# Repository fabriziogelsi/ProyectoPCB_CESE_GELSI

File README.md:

# ProyectoPCB_CESE_GELSI
Diseño de shield RF para portar a la EDU-CIAA

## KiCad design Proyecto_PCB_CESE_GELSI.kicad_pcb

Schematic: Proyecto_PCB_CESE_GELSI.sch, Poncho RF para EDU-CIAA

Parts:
ANT1: Antenna; antena
C1: 22uF; C_0805_HandSoldering; Digikey# 490-7611-1-ND
C2, C3, C4, C5, C6: 100nF; C_0805_HandSoldering; Digikey# 478-5266-1-ND
D2: LED_ALT; D_0805; Digikey# 475-1410-1-ND
F1, F2, F3: FIDUCIAL; Fiducial_1mm
IC1: SC2272L4; SSOP-20_5.3x7.2mm_Pitch0.65mm
IC2: ASM1117-33; SOT-223; Digikey# NCP1117ST50T3GOSCT-ND
IC3: SN74LVC1G125DCKR; SC-70-5; Digikey# 296-11604-1-ND
IC4: H5V3G
R2, R3: 1k; R_0805_HandSoldering; Digikey# 311-1.00KFRCT-ND
R4: 22; R_0805_HandSoldering; Digikey# 311-22ERCT-ND
R5: 620k; R_0805_HandSoldering; Digikey# 311-620KFRCT-ND
S1: SW SPDT; SW_SPDT; Digikey# 679-1847-6-ND
XA1: Conn_Poncho2P_2x_20x2; Conn_Poncho_Completo
Xbee1: XBee_Header; XBEE-HEADER; Digikey# 1528-1392-ND

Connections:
+3.3V: C3.1, C4.1, C5.1, IC2.2 (VO), IC3.5 (VCC), Xbee1.1 (VCC)
+5V: C1.1, C2.1, C6.1, IC1.20 (VCC), IC2.3 (VI), IC4.3 (VCC), XA1.2 (+5V), XA1.42 (+5V)
GND: C1.2, C2.2, C3.2, C4.2, C5.2, C6.2, D2.1 (K), IC1.9 (VSS), IC2.1 (GND/ADJ), IC3.1 (!OE!), IC3.3 (GND), IC4.2 (GND), IC4.6 (GND), XA1.43 (GND), XA1.79 (GND), Xbee1.10 (GND)
unnamed: ANT1.1, IC4.1 (ANT)
unnamed: D2.2 (A), R2.2
unnamed: IC1.1 (A0), XA1.66 (lcd3)
unnamed: IC1.2 (A1), XA1.68 (lcd2)
unnamed: IC1.3 (A2), XA1.70 (lcd1)
unnamed: IC1.4 (A3), XA1.72 (GPIO1)
unnamed: IC1.5 (A4), XA1.74 (GPIO3)
unnamed: IC1.6 (A5), XA1.76 (GPIO5)
unnamed: IC1.7 (A6), XA1.78 (GPIO7)
unnamed: IC1.8 (A7), XA1.80 (GPIO8)
unnamed: IC1.12 (A8), XA1.75 (GPIO6)
unnamed: IC1.13 (A9), XA1.73 (GPIO4)
unnamed: IC1.14 (A10), XA1.71 (GPIO2)
unnamed: IC1.15 (A11), XA1.69 (GPIO0)
unnamed: IC1.16 (DIN), IC4.4 (DAT), IC4.5 (DAT)
unnamed: IC1.17 (OSCO), R5.1
unnamed: IC1.18 (OSCI), R5.2
unnamed: IC1.19 (VT), XA1.63 (lcdEN)
unnamed: IC3.2 (A), R3.1
unnamed: IC3.4 (Y), Xbee1.3 (DIN/~CONFIG)
unnamed: R2.1, Xbee1.15 (Assoc./AD5/DIO5)
unnamed: R3.2, XA1.25 (rs232TXD)
unnamed: R4.1, Xbee1.2 (DOUT)
unnamed: R4.2, S1.1 (A)
unnamed: S1.2 (B), XA1.23 (rs232RXD)

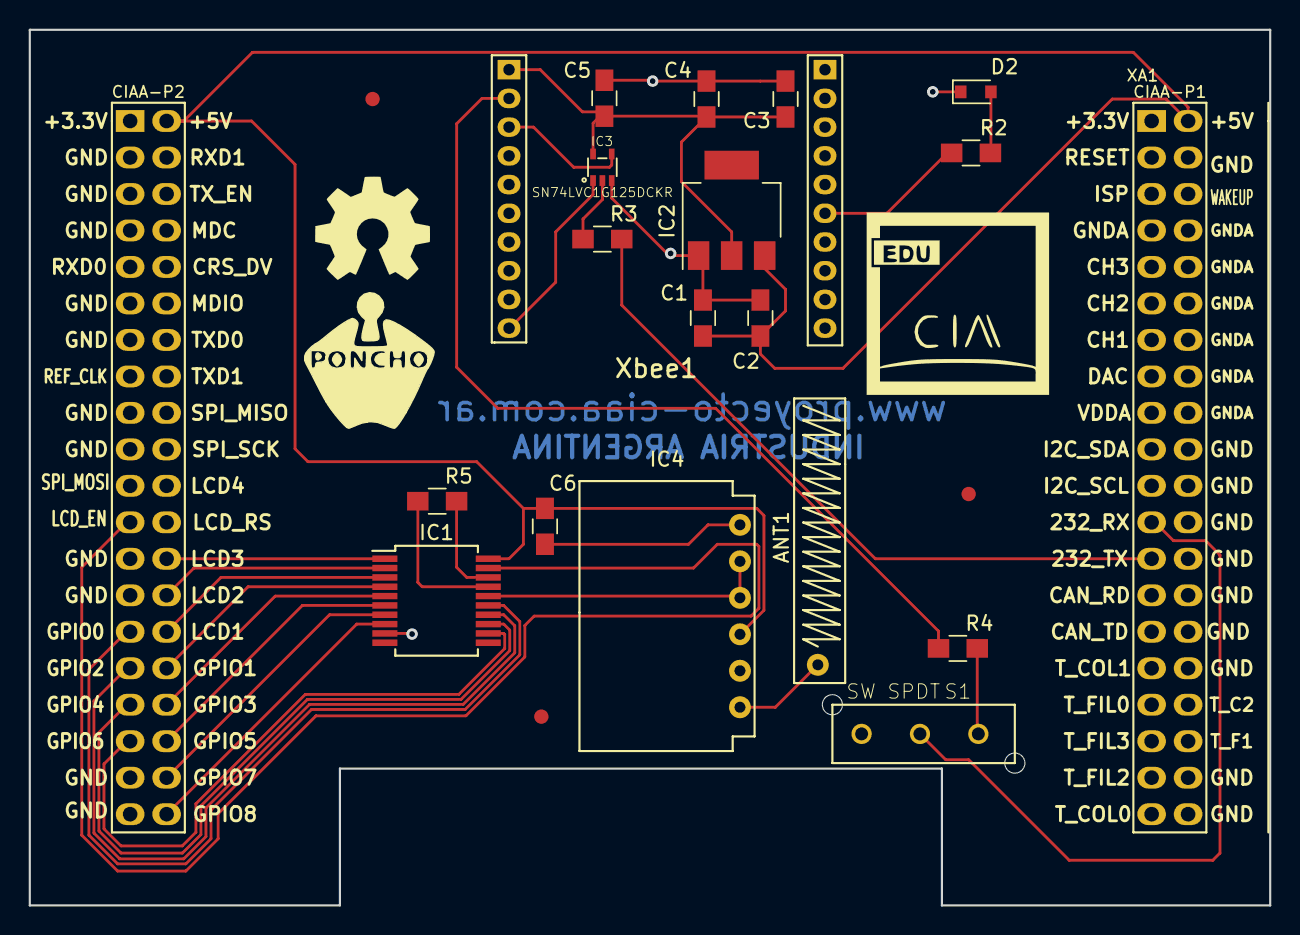
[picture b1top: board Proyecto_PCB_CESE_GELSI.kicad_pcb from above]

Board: 2 copper layers, 86.4 x 61.0 mm, 23 parts (0 on the bottom side), 28 nets.

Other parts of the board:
G101: Logo_OSHWA

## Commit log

2017-05-13 Creación del proyecto en kicad
    Sólo se creó el proyecto en kicad para desarrollar el poncho de RF para la EDU-CIAA, y se rellenaron algunos datos del rótulo
2017-05-14 Update en esquemático
    Se avanzó sobre el esquemático, lo que incluyó incorporación de nuevas librerías.
2017-05-26 Avance en el esquemático y reorganización de archivos
2017-06-01 Avance hacia cierre de esquemático y comienzo de pcb
    Falta sólo realizar comentarios con etiquetas en el esquemático, de los subsistemas. Y por otro lado ya se comenzó con el pcb, se avanzó para poder preguntar en clases dudas respecto al tema de rutea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
2017-06-18 Update en el proyecto
    Se consolidaron datos en la mayoría de los componentes, como fabricante, parte dentro del fabricante, digikey, y descripción
2017-06-20 Revision de esquematico
2017-06-20 Update en proyecto
    Correciones realizadas luego de que fueran marcadas por el revisor. Además se incorporó una única carpeta de librearías, que era en lo que venía trabajándose para llegar a esto antes de la primer ent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
2017-07-09 Update en el proyecto (Correcciones parciales de 1ra fecha)
    Se corrigieron algunas cosas marcadas en la 1ra fecha.
2017-07-12 Update en proyecto (OK Esquemático y asociación)
    Se realizaron todos los fixes necesarios para dejar OK los errores marcados en la sección "Esquemático" y "Asociación".
2017-07-15 Update en proyecto
    Se resolvieron algunos problemas referidos al PCB, a fin de corregir los errores marcados durante la primer entrega. Por problemas con el IDE KICAD, se dejaron algunos para la tercer entrega.
2017-07-29 Correciones totales al esquemático, pcb y organización parcial en visor 3D
2017-07-31 Update final a producción.
    Subida final de archivos para sustentar las cosas a corregir marcadas por el profesor. Faltantes no conseguidos en visión 3D.
